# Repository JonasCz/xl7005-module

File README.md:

# xl7005-module

XL7005-based DC-DC converter module design, with optional space for LDO for lower-voltage rails.

**PCB layout, XL7005 side:**

(Populating the other side is optional, it features space for an LDO)

**Schematic:**

**Status:** Tested, everything works.

**Features:**

* XT30 input and output connectors for main input and ouptut
* Features space for an optional LDO to provide a low-power rail for e.g. a microcontroller. If not populated, the back of the board is empty. Can be any of the common SOT223 "1117" style.
* 2 Layer.

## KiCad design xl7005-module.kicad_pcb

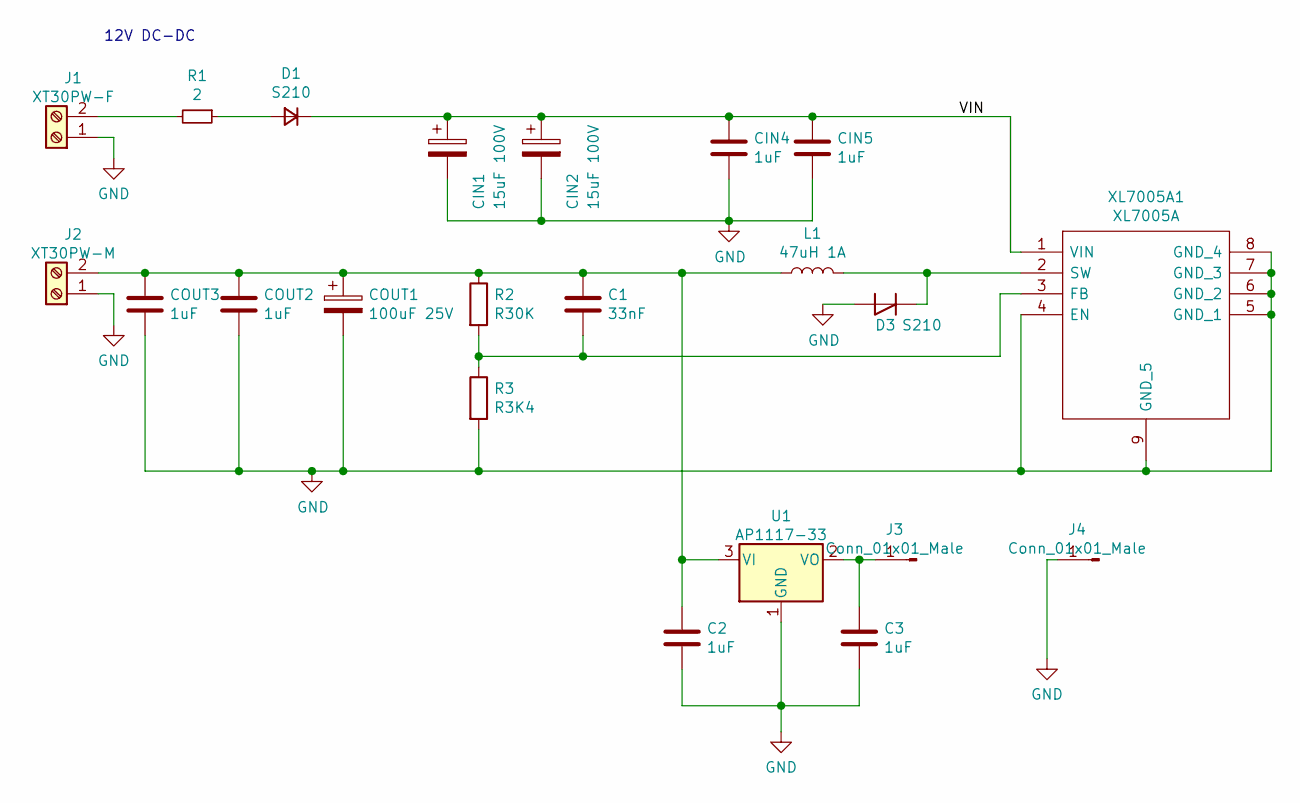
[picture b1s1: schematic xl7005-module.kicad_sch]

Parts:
C1: 33nF; C_0805_2012Metric; LCSC Part Number C525305
C2, C3: 1uF; C_0805_2012Metric; LCSC Part Number C28323
CIN1, CIN2: 15uF 100V; CP_Radial_D6.3mm_P2.50mm; LCSC Part Number C270029
CIN4, CIN5: 1uF; C_1210_3225Metric; LCSC Part Number C840122
COUT1: 100uF 25V; CP_Radial_D6.3mm_P2.50mm; LCSC Part Number C216321
COUT2, COUT3: 1uF; C_1210_3225Metric; LCSC Part Number C840122
D1: S210; D_SMA; LCSC Part Number C14996
D3: S210; D_SOD-123; LCSC Part Number C14996
J1: XT30PW-F; AMASS_XT30PW-F_1x02_P2.50mm_Horizontal
J2: XT30PW-M; AMASS_XT30PW-M_1x02_P2.50mm_Horizontal; LCSC Part Number C431092
J3, J4: Conn_01x01_Male; SolderWirePad_1x01_SMD_1x2mm
L1: 47uH 1A; L_7.3x7.3_H4.5; LCSC Part Number C439282
R1: 2; R_1210_3225Metric; LCSC Part Number C105000
R2: R30K; R_0805_2012Metric; LCSC Part Number C702861
R3: R3K4; R_0805_2012Metric; LCSC Part Number C17608
U1: AP1117-33; SOT-223-3_TabPin2; LCSC Part Number C83972
XL7005A1: XL7005A; SOIC127P600X175-9N; Manufacturer_Part_Number XL7005A; LCSC Part Number C50848

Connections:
/VIN: CIN1.1, CIN2.1, CIN4.1, CIN5.1, D1.1 (K), XL7005A1.1 (VIN)
GND: C2.2, C3.2, CIN1.2, CIN2.2, CIN4.2, CIN5.2, COUT1.2, COUT2.2, COUT3.2, D3.2 (A), J1.1, J2.1, J4.1, R3.2, U1.1 (GND), XL7005A1.4 (EN), XL7005A1.5 (GND_1), XL7005A1.6 (GND_2), XL7005A1.7 (GND_3), XL7005A1.8 (GND_4), XL7005A1.9 (GND_5)
unnamed: C1.1, C2.1, COUT1.1, COUT2.1, COUT3.1, J2.2, L1.1, R2.1, U1.3 (VI)
unnamed: C1.2, R2.2, R3.1, XL7005A1.3 (FB)
unnamed: D1.2 (A), R1.1
unnamed: D3.1 (K), L1.2, XL7005A1.2 (SW)
unnamed: J1.2, R1.2
unnamed: C3.1, J3.1, U1.2 (VO)

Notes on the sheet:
12V DC-DC

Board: 2 copper layers, 22 parts (5 on the bottom side), 8 nets, no tracks yet.
